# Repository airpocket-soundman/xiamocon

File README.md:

# xiamocon
Game Console-Shaped Motherboard for XIAO RP2350/ESP32S3

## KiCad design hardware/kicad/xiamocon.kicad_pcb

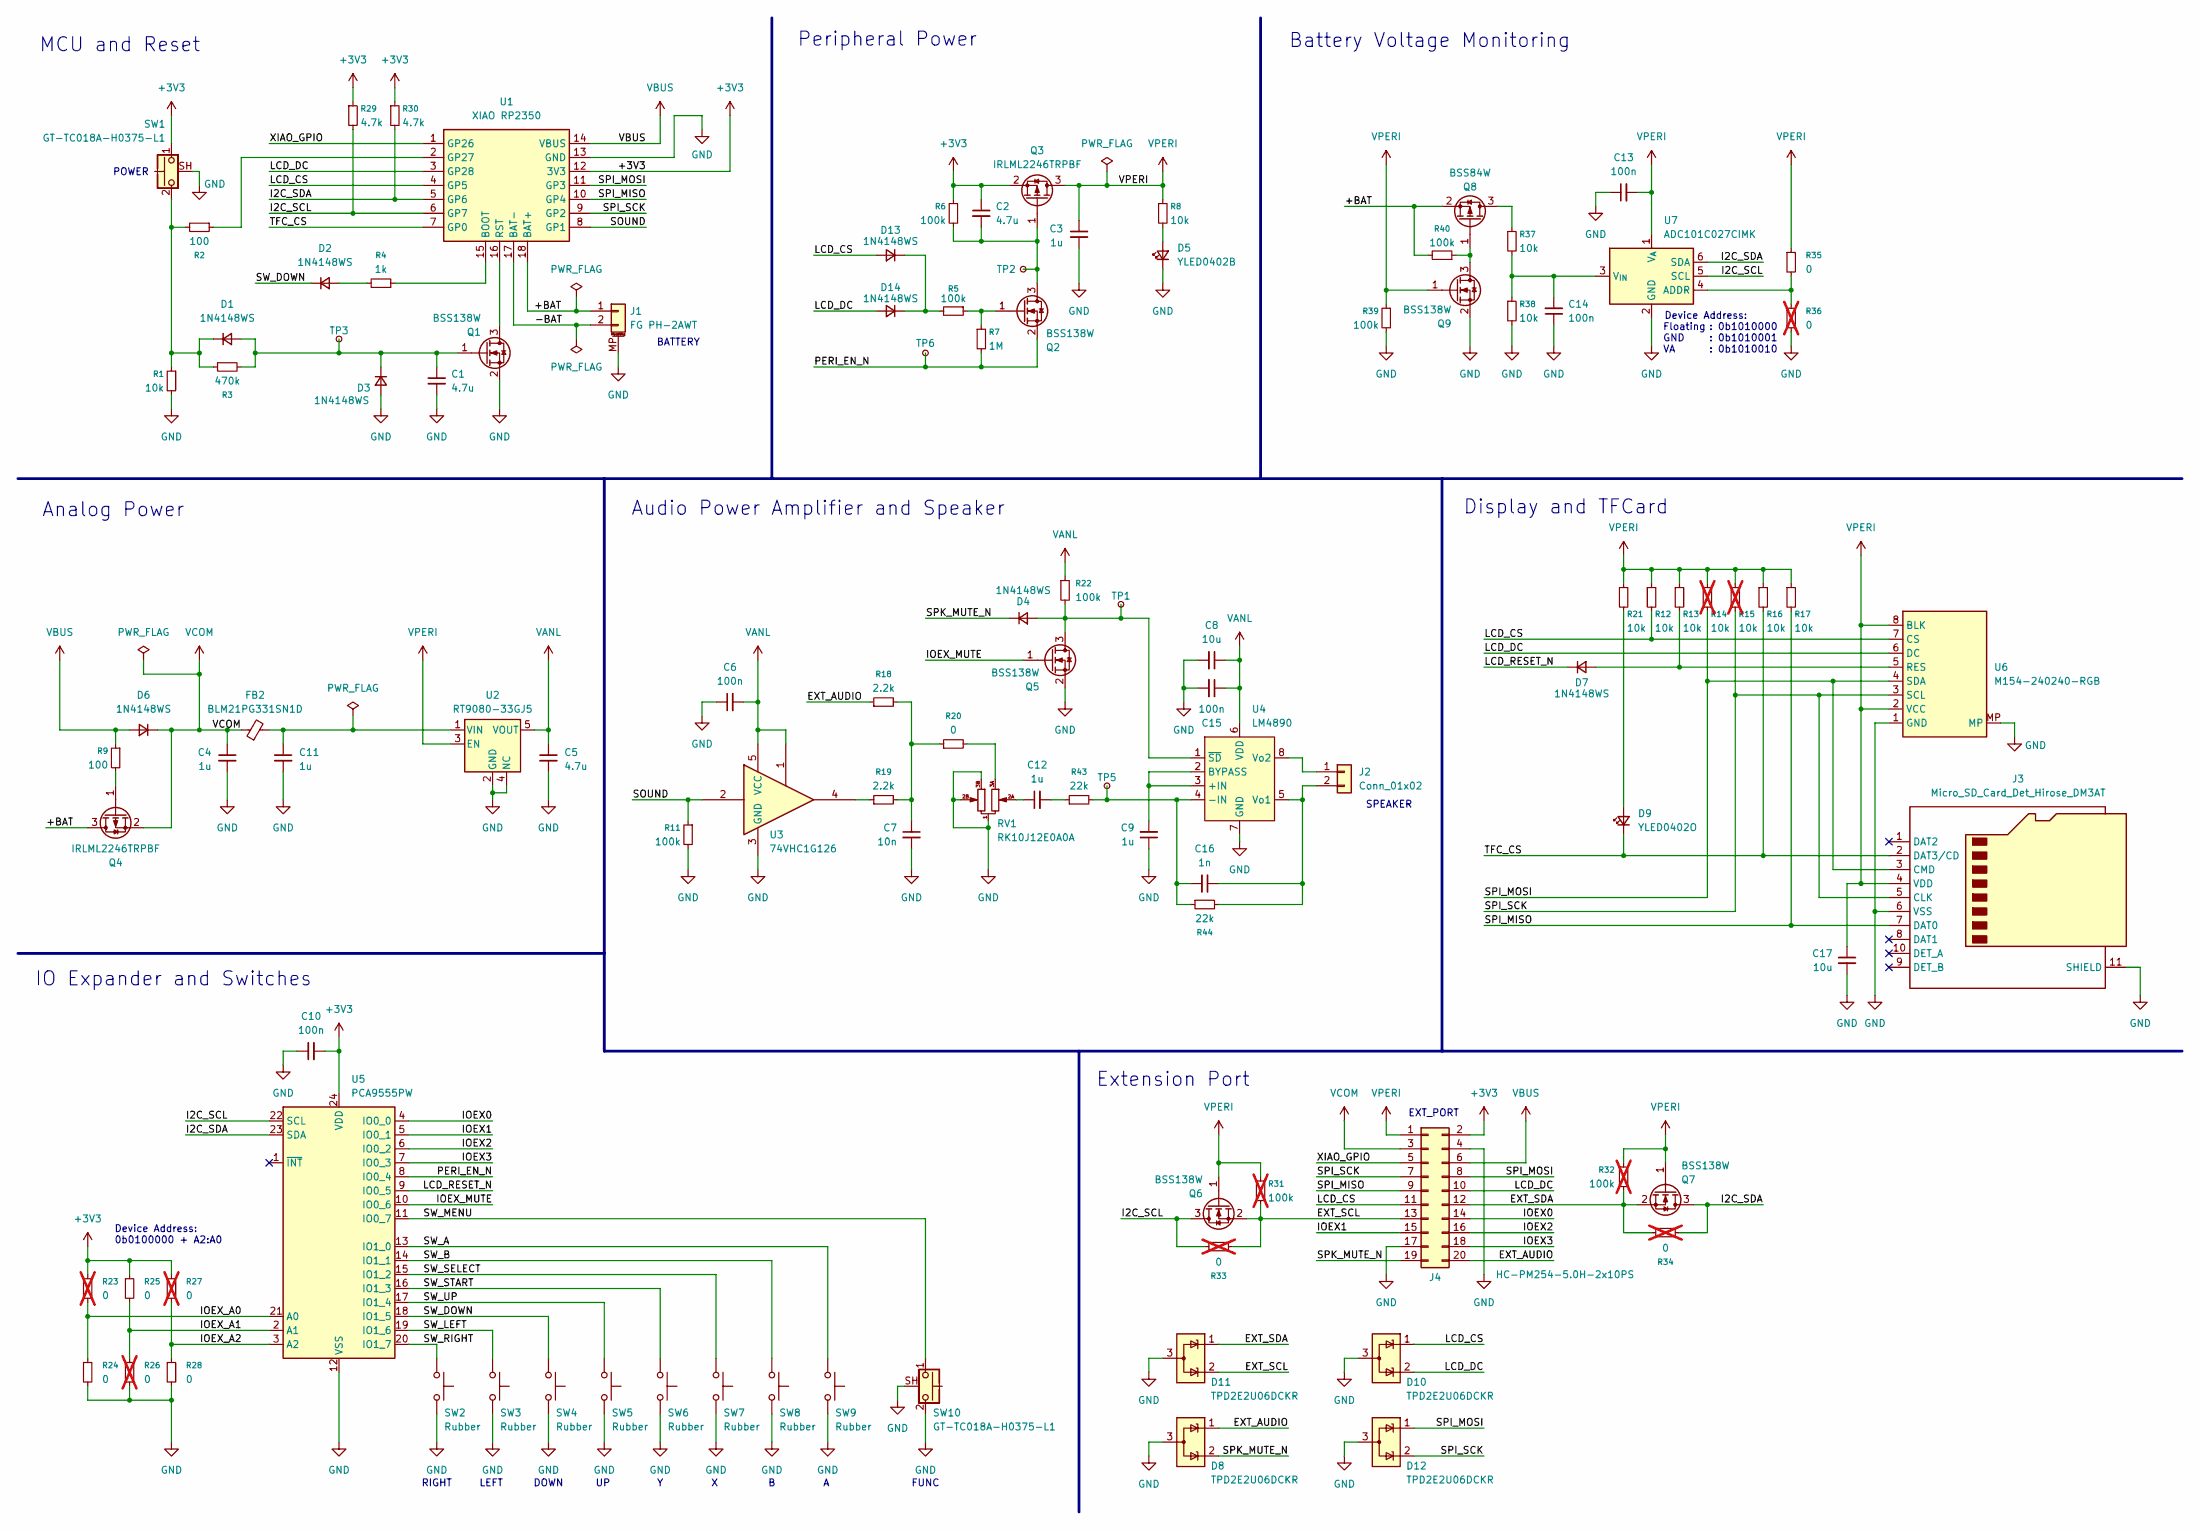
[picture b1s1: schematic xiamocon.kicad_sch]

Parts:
C1, C2, C5: 4.7u; C_0603_1608Metric; LCSC C19666
C3, C4, C11: 1u; C_0402_1005Metric; LCSC C52923
C6, C10, C13, C14, C15: 100n; C_0402_1005Metric; LCSC C1525
C7: 10n; C_0402_1005Metric; LCSC C15195
C8, C17: 10u; C_0603_1608Metric; LCSC C1691
C9, C12: 1u; C_0603_1608Metric; LCSC C15849
C16: 1n; C_0402_1005Metric; LCSC C1523
D1, D2, D3, D4, D7, D13, D14: 1N4148WS; D_SOD-523; LCSC C917006
D5: YLED0402B; LED_0402_1005Metric_Pad0.77x0.64mm_HandSolder; LCSC C30584803
D6: 1N4148WS; D_SOD-323; LCSC C2128
D8, D10, D11, D12: TPD2E2U06DCKR; SOT-323_SC-70; LCSC C1855726
D9: YLED0402O; LED_0402_1005Metric_Pad0.77x0.64mm_HandSolder; LCSC C28310436
FB2: BLM21PG331SN1D; L_0805_2012Metric; LCSC C74764
J1: FG PH-2AWT; JST_PH_S2B-PH-SM4-TB_1x02-1MP_P2.00mm_Horizontal; LCSC C2763693
J2: Conn_01x02; SolderWirePad_1x02_SMD_150x50mil
J3: Micro_SD_Card_Det_Hirose_DM3AT; microSD_HC_Hirose_DM3AT-SF-PEJM5; LCSC C114218
J4: HC-PM254-5.0H-2x10PS; PinSocket_2x10_P2.54mm_Vertical_SMD; LCSC C42163138
Q1, Q2, Q5, Q6, Q7, Q9: BSS138W; SOT-323_SC-70; LCSC C504052
Q3, Q4: IRLML2246TRPBF; SOT-23; LCSC C127272
Q8: BSS84W; SOT-323_SC-70; LCSC C919394
R1, R12, R13, R16, R17, R37, R38: 10k; R_0402_1005Metric; LCSC C25744
R2, R9: 100; R_0402_1005Metric; LCSC C25076
R3: 470k; R_0402_1005Metric; LCSC C137976
R4: 1k; R_0402_1005Metric; LCSC C11702
R5, R6, R11, R22, R39, R40: 100k; R_0402_1005Metric; LCSC C25741
R7: 1M; R_0402_1005Metric; LCSC C26083
R8, R21: 10k; R_0402_1005Metric_Pad0.72x0.64mm_HandSolder; LCSC C25744
R14, R15: 10k; R_0402_1005Metric; LCSC C25744; not fitted
R18, R19: 2.2k; R_0402_1005Metric; LCSC C25879
R20, R24, R25, R28, R35: 0; R_0402_1005Metric; LCSC C17168
R23, R26, R27, R33, R34, R36: 0; R_0402_1005Metric; LCSC C17168; not fitted
R29, R30: 4.7k; R_0402_1005Metric; LCSC C25900
R31, R32: 100k; R_0402_1005Metric; LCSC C25741; not fitted
R43, R44: 22k; R_0402_1005Metric; LCSC C25768
RV1: RK10J12E0A0A; RK10J1xE; LCSC C351176
SW1, SW10: GT-TC018A-H0375-L1; LCSC C963235
SW2, SW3, SW4, SW5, SW6, SW7, SW8, SW9: Rubber; Rubber_Contact
TP1, TP2, TP3, TP5, TP6: PWAMP_CE; TestPoint_Pad_D1.5mm
U1: XIAO RP2350
U2: RT9080-33GJ5; TSOT-23-5; LCSC C841192
U3: 74VHC1G126; SOT-23-5; LCSC C53100485
U4: LM4890; MSOP-8_3x3mm_P0.65mm; LCSC C329452
U5: PCA9555PW; TSSOP-24_4.4x7.8mm_P0.65mm; LCSC C128392
U6: M154-240240-RGB
U7: ADC101C027CIMK; TSOT-23-6; LCSC C701590

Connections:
+3V3: C2.1, C10.2, J4.2, Q3.2 (S), R6.1, R23.1, R25.1, R27.1, R29.1, R30.1, SW1.1, U1.12 (3V3), U5.24 (VDD)
/+BAT: J1.1, Q4.3 (D), Q8.2 (S), R40.2, U1.18 (BAT+)
/-BAT: J1.2, U1.17 (BAT-)
/EXT_AUDIO: D8.1 (K), J4.20, R18.1
/EXT_SCL: D11.2 (K), J4.13, Q6.2 (S), R31.2, R33.2
/EXT_SDA: D11.1 (K), J4.12, Q7.2 (S), R32.2, R34.1
/I2C_SCL: Q6.3 (D), R29.2, R33.1, U1.6 (GP7), U5.22 (SCL), U7.5 (SCL)
/I2C_SDA: Q7.3 (D), R30.2, R34.2, U1.5 (GP6), U5.23 (SDA), U7.6 (SDA)
/IOEX0: J4.14, U5.4 (IO0_0)
/IOEX1: J4.15, U5.5 (IO0_1)
/IOEX2: J4.16, U5.6 (IO0_2)
/IOEX3: J4.18, U5.7 (IO0_3)
/IOEX_A0: R23.2, R24.1, U5.21 (A0)
/IOEX_A1: R25.2, R26.1, U5.2 (A1)
/IOEX_A2: R27.2, R28.1, U5.3 (A2)
/IOEX_MUTE: Q5.1 (G), U5.10 (IO0_6)
/LCD_CS: D10.1 (K), D13.2 (A), J4.11, R12.2, U1.4 (GP5), U6.7 (CS)
/LCD_DC: D10.2 (K), D14.2 (A), J4.10, U1.3 (GP28), U6.6 (DC)
/LCD_RESET_N: D7.1 (K), U5.9 (IO0_5)
/PERI_EN_N: Q2.2 (S), R7.2, TP6.1, U5.8 (IO0_4)
/SOUND: R11.1, U1.8 (GP1), U3.2
/SPI_MISO: J3.7 (DAT0), J4.9, R17.2, U1.10 (GP4)
/SPI_MOSI: D12.1 (K), J3.3 (CMD), J4.8, R14.2, U1.11 (GP3), U6.4 (SDA)
/SPI_SCK: D12.2 (K), J3.5 (CLK), J4.7, R15.2, U1.9 (GP2), U6.3 (SCL)
/SPK_MUTE_N: D4.1 (K), D8.2 (K), J4.19
/SW_A: SW9.1, U5.13 (IO1_0)
/SW_B: SW8.1, U5.14 (IO1_1)
/SW_DOWN: D2.1 (K), SW4.1, U5.18 (IO1_5)
/SW_LEFT: SW3.1, U5.19 (IO1_6)
/SW_MENU: SW10.1, U5.11 (IO0_7)
/SW_RIGHT: SW2.1, U5.20 (IO1_7)
/SW_SELECT: SW7.1, U5.15 (IO1_2)
/SW_START: SW6.1, U5.16 (IO1_3)
/SW_UP: SW5.1, U5.17 (IO1_4)
/TFC_CS: D9.1 (K), J3.2 (DAT3/CD), R16.2, U1.7 (GP0)
/XIAO_GPIO: J4.5, U1.1 (GP26)
GND: C1.2, C3.2, C4.2, C5.2, C6.1, C7.2, C8.2, C9.1, C10.1, C11.2, C13.1, C14.1, C15.2, C17.2, D3.2 (A), D5.1 (K), D8.3 (A), D10.3 (A), D11.3 (A), D12.3 (A), J1.MP (MountPin), J3.6 (VSS), J3.11 (SHIELD), J4.4, J4.17, Q1.2 (S), Q5.2 (S), Q9.2 (S), R1.2, R11.2, R24.2, R26.2, R28.2, R36.2, R38.2, R39.2, RV1.1, RV1.2B, RV1.3B, SW1.SH (B), SW2.2, SW3.2, SW4.2, SW5.2, SW6.2, SW7.2, SW8.2, SW9.2, SW10.2, SW10.SH (B), U1.13 (GND), U2.2 (GND), U2.4 (NC), U3.3 (GND), U4.7 (GND), U5.12 (VSS), U6.1 (GND), U6.MP, U7.2 (GND)
unnamed: C7.1, R18.2, R19.2, R20.1
unnamed: C12.1, RV1.2A
unnamed: C12.2, R43.1
unnamed: C1.1, D1.2 (A), D3.1 (K), Q1.1 (G), R3.2, TP3.1
unnamed: D1.1 (K), R1.1, R2.2, R3.1, SW1.2
unnamed: D2.2 (A), R4.2
unnamed: D4.2 (A), Q5.3 (D), R22.2, TP1.1, U4.1 (~SD)
unnamed: D5.2 (A), R8.2
unnamed: D7.2 (A), R13.2, U6.5 (RES)
unnamed: D9.2 (A), R21.2
unnamed: D13.1 (K), D14.1 (K), R5.2
unnamed: J2.1, U4.8 (Vo2)
unnamed: C16.1, J2.2, R44.2, U4.5 (Vo1)
unnamed: Q1.3 (D), U1.16 (RST)
unnamed: C2.2, Q2.3 (D), Q3.1 (G), R6.2, TP2.1
unnamed: Q2.1 (G), R5.1, R7.1
unnamed: Q4.1 (G), R9.2
unnamed: Q8.3 (D), R37.1
unnamed: Q8.1 (G), Q9.3 (D), R40.1
unnamed: R19.1, U3.4
unnamed: R20.2, RV1.3A
unnamed: R4.1, U1.15 (BOOT)
unnamed: R2.1, U1.2 (GP27)
unnamed: C11.1, FB2.2, U2.1 (VIN)
unnamed: C9.2, U4.2 (BYPASS), U4.3 (+IN)
unnamed: C16.2, R43.2, R44.1, TP5.1, U4.4 (-IN)
unnamed: R35.2, R36.1, U7.4 (ADDR)
unnamed: C14.2, R37.2, R38.1, U7.3 (V_{IN})
VANL: C5.1, C6.2, C8.1, C15.1, R22.1, U2.5 (VOUT), U3.1, U3.5 (VCC), U4.6 (VDD)
VBUS: D6.2 (A), J4.6, R9.1, U1.14 (VBUS)
VCOM: C4.1, D6.1 (K), FB2.1, J4.3, Q4.2 (S)
VPERI: C3.1, C13.2, C17.1, J3.4 (VDD), J4.1, Q3.3 (D), Q6.1 (G), Q7.1 (G), Q9.1 (G), R8.1, R12.1, R13.1, R14.1, R15.1, R16.1, R17.1, R21.1, R31.1, R32.1, R35.1, R39.1, U2.3 (EN), U6.2 (VCC), U6.8 (BLK), U7.1 (V_{A})

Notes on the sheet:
LEFT
BATTERY
Display and TFCard
Audio Power Amplifier and Speaker
DOWN
Device Address:
Extension Port
RIGHT
Floating GND VA
SPEAKER
Peripheral Power
Device Address: 0b0100000 + A2:A0
Battery Voltage Monitoring
MCU and Reset
EXT_PORT
POWER
IO Expander and Switches
: 0b1010000 : 0b1010001 : 0b1010010
FUNC
Analog Power

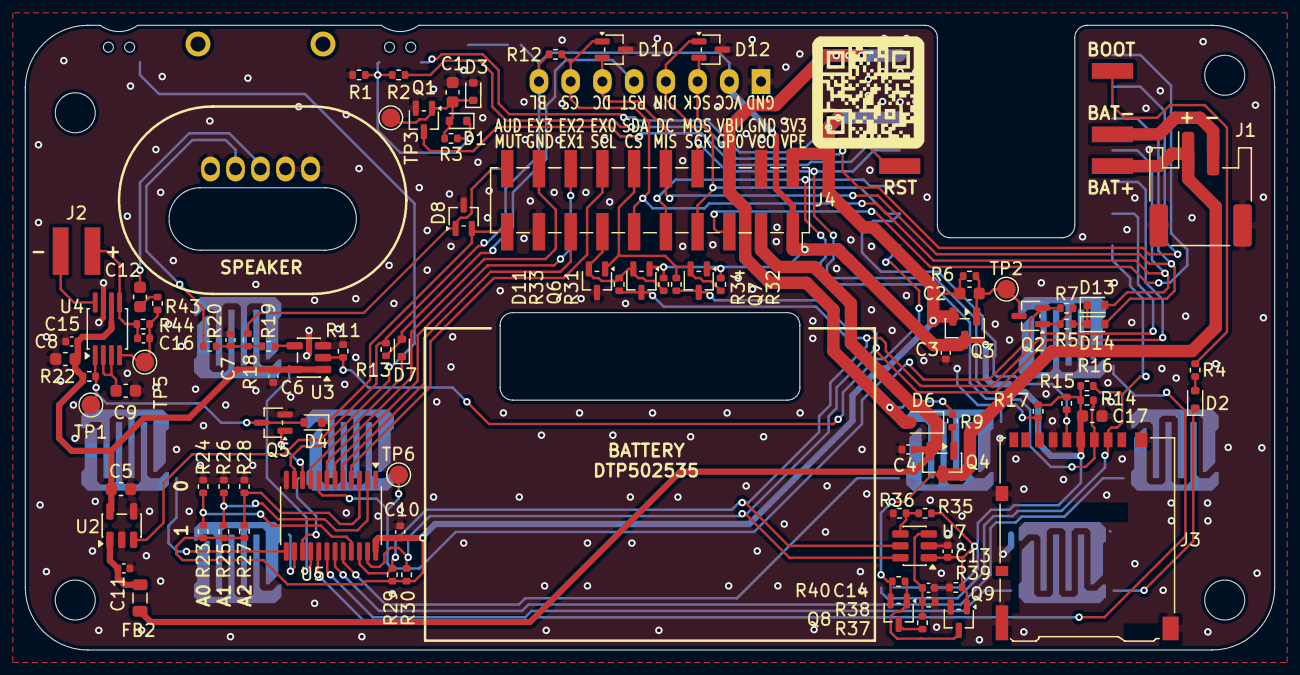
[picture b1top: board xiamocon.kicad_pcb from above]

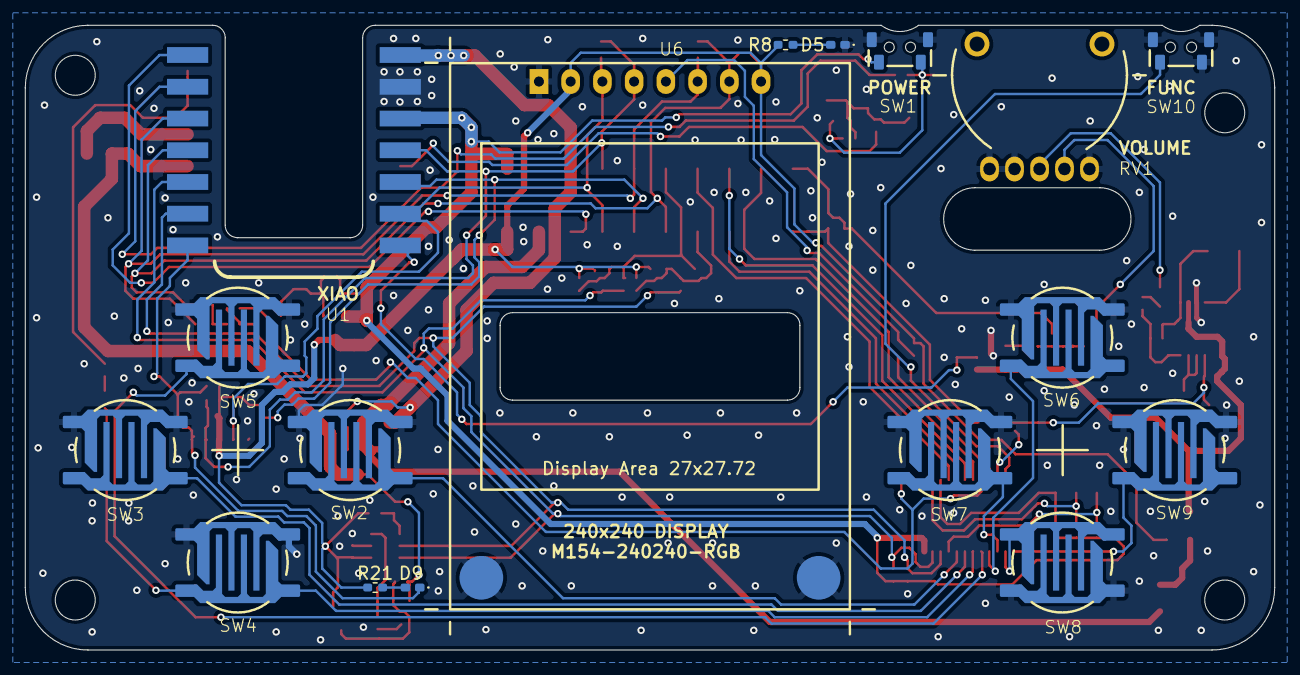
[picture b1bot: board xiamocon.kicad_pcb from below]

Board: 2 copper layers, 100.0 x 50.0 mm, 109 parts (17 on the bottom side), 69 nets.

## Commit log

2026-03-07 change directory structure
2026-03-12 schematic fixed
2026-03-16 pcb rev2 checked
2026-03-16 pcb rev.2 ordered
2026-03-21 renamed: .c/.h-->.cpp/.hpp
2026-03-24 wip: glTF converter tool
2026-03-26 AtomS3用デモ制作中
